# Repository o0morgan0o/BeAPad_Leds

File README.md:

# BeAPad Led Project

Project for touch sensors combined to Neopixels and RTP Midi for controlling Light and music via midiMessages across wifi.

## Materials:

- ESP32 Microcontroller (WROOM
  DEVKIT_V1) [amazon](https://www.amazon.fr/SP-Cow-ESP-32S-d%C3%A9veloppement-Bluetooth-d%C3%A9nergie/dp/B07VJ34N2Q/ref=sr_1_5?__mk_fr_FR=%C3%85M%C3%85%C5%BD%C3%95%C3%91&crid=2QX1H1678O7M3&keywords=esp32+wroom+devkit&qid=1652459031&sprefix=esp32+wroom+devkit%2Caps%2C51&sr=8-5) [aliexpress](https://fr.aliexpress.com/item/1005001929935550.html?spm=a2g0o.search0304.0.0.a4b41103QWyj6D&algo_pvid=caa6f633-4206-442e-8846-f58ec6503b21&algo_exp_id=caa6f633-4206-442e-8846-f58ec6503b21-0&pdp_ext_f=%7B%22sku_id%22%3A%2212000022802021515%22%7D&pdp_npi=2%40dis%21EUR%21%2127.77%21%21%21%21%21%402100bdca16524589488372088ea014%2112000022802021515%21sea)
- MPR121 Touch Shield [amazon](https://www.amazon.fr/Adafruit-12-Key-Capacitive-Sensor-Breakout/dp/B00SK8PVNA)
- WS2812E leds [amazon](https://www.amazon.fr/gp/product/B088BRY2SH/ref=ppx_yo_dt_b_asin_title_o07_s00?ie=UTF8&th=1) **<u>MUST BE 60Leds/m for easy soldering on PCB</u>**
- Battery 1100 mAh Lithium 1S 3c
- 1 Capacitor 1000uF
- Steel plates
- Optional : Power Supply 5V 10A or 4 AA Batteries

## Usage

Use RTP-Midi software in windows to listen for midi signals over Wi-Fi.
(software : https://www.tobias-erichsen.de/software/rtpmidi/rtpmidi-tutorial.html)

Set RTP-Midi device to address `192.168.0.4` (address set to client by ESP32 DHCP)

## Ableton Setup

In order to send midi towards the controller, on each midi track, set an instrument rack with:
- External instrument to RTP_Midi Receiver session
- Your drum rack with active notes mentioned in next section

### Mapping MidiReceive

```
Each MidiNote Receveid is connected to a specific light effect on board
 _______________________________________
|  | | | |  |  | | | | | |  |  | | | |  |
|  | | | |  |  | | | | | |  |  | | | |  |
|  | | | |  |  | | | | | |  |  | | | |  |
|  |_| |_|  |  |_| |_| |_|  |  |_| |_|  |
|   |   |   |   |   |   |   |   |   |   |
|   |   |   |   |   |   |   |   |   |   |
|___|___|___|___|___|___|___|___|___|___|

TOUCH SENSOR BOARDS ARE CONNECTED TO THE FOLLOWING MIDI NOTES:
  The boards always send the same midiNote:
    -> C4 ( MIDI 60 )      Board 1
    -> C#4 ( MIDI 61 )     Board 2
    -> D4 ( MIDI 62 )      Board 3
    -> D#4 ( MIDI 63 )     Board 4
    -> E4 ( MIDI 64 )      Board 5
    -> F4 ( MIDI 65 )      Board 6
    -> F#4 ( MIDI 66 )     Board 7
    -> G4 ( MIDI 67 )      Board 8
    -> G#4 ( MIDI 68 )     Board 9
    -> A4 ( MIDI 69 )      Board 10
    -> A#4 ( MIDI 70 )     Board 11
    
WHEN SHIFT IS PRESSED (BOARD 12) THE SENSOR BOARDS CAN SEND THESE MIDI NOTES:
    ->  G#6 ( MIDI 80 )     Board 1
    ->  A6 ( MIDI 81 )      Board 2
    ->  A#6 ( MIDI 82 )     Board 3
    ->  B6 ( MIDI 83 )      Board 4
    ->  C7 ( MIDI 84 )      Board 5
    ->  C#7 ( MIDI 85 )     Board 6
    ->  D7 ( MIDI 86 )      Board 7
    ->  D#7 ( MIDI 87 )     Board 8
    ->  E7 ( MIDI 88 )      Board 9
    ->  F7 ( MIDI 89 )      Board 10
    ->  F#7 ( MIDI 90 )     Board 11

*****************************
LIGHT_STRATEGIES PER CHANNEL:
-> One color per channel
*****************************
    CHANNEL 1 | FULL_LIGHT
    CHANNEL 2 | FADE_OUT
    CHANNEL 3 | SERPENTIN
    CHANNEL 4 | FLASH_TOWARDS_EXTERIOR
    CHANNEL 5 | NOTHING YET
    CHANNEL 6 | NOTHING YET
    CHANNEL 7 | NOTHING YET
    CHANNEL 8 | NOTHING YET
    
******************************
SPECIAL EFFECTS
-> Color can be change by midi_note value
-> Luminosity can be change by velocity value
******************************

    CHANNEL 9  | STROMBOSCOPE
    CHANNEL 10 | NOTHING YET
    CHANNEL 11 | NOTHING YET
    CHANNEL 12 | NOTHING YET
    CHANNEL 13 | NOTHING YET
    CHANNEL 14 | NOTHING YET
    CHANNEL 15 | NOTHING YET
    CHANNEL 16 | NOTHING YET

```

## Hardware

### LedBoards:

(See EasyEDA project in "Resources_PCB_Schematics")

**Warning: Orientation of led change across the board (see real reference below)**

### Controller Board

(See KiCad project in "Resources_PCB_Schematics")

**Real prototype**

### 3D Models

Very basic holders can be found in Resources_3D_printing.

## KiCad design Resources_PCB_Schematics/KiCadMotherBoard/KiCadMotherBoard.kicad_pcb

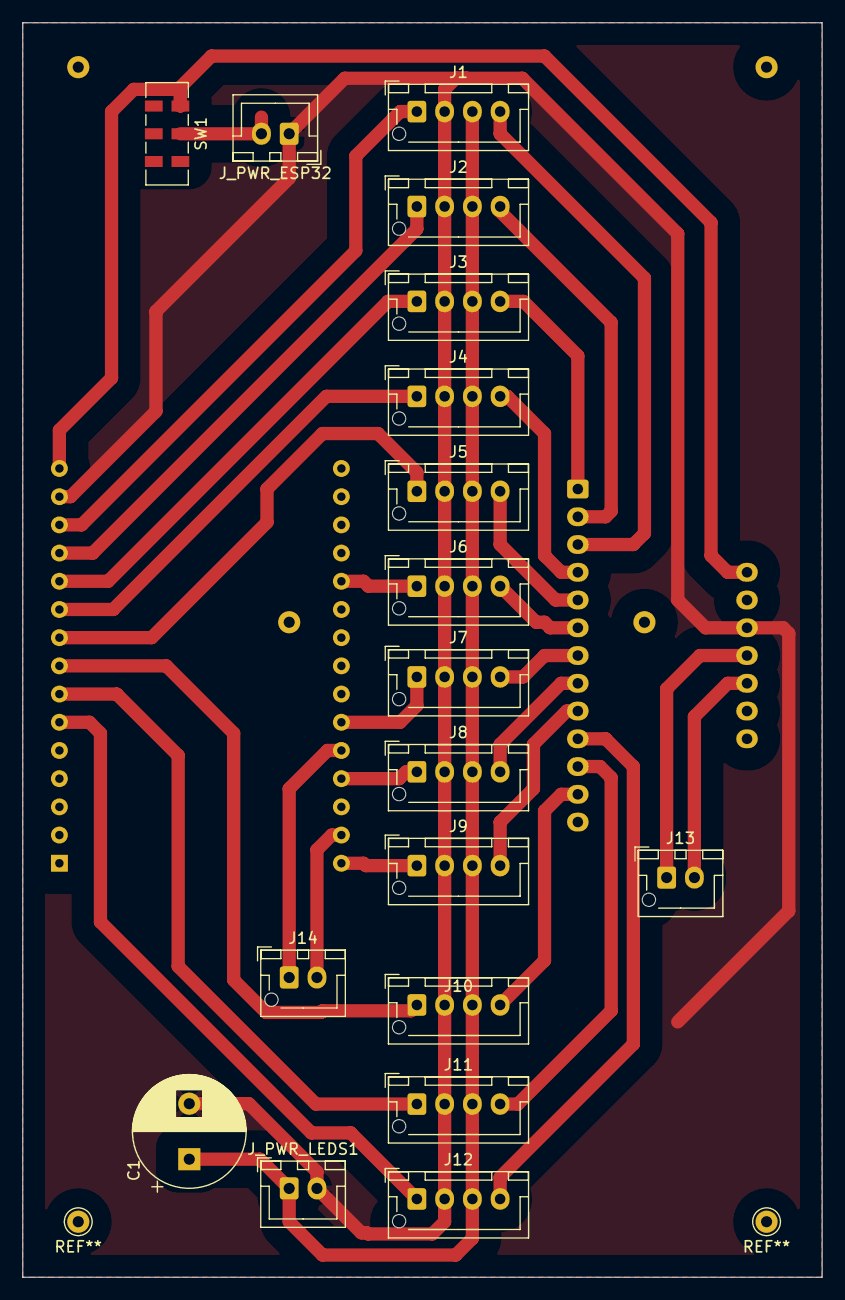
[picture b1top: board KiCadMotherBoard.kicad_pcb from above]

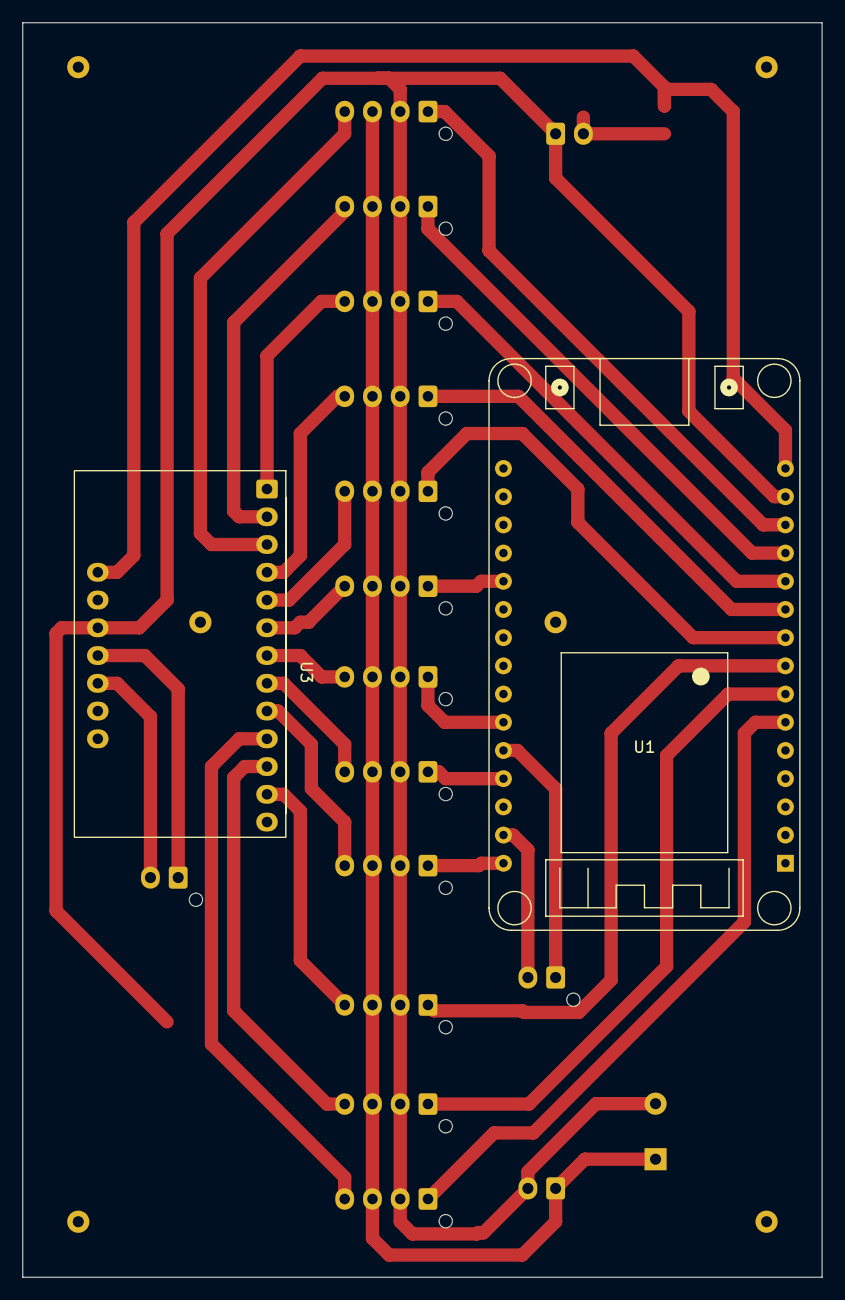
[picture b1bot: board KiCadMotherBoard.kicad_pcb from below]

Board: 2 copper layers, 72.0 x 113.0 mm, 20 parts (2 on the bottom side), 30 nets.

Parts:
C1: 1000uF; CP_Radial_D10.0mm_P5.00mm
J1, J2, J3, J4, J5, J6, J7, J8, J9, J10, J11, J12: Conn_01x04_Male; JST_XH_B4B-XH-AM_1x04_P2.50mm_Vertical
J13, J14: SDA_SCL_BRIDGE; JST_XH_B2B-XH-AM_1x02_P2.50mm_Vertical
J_PWR_ESP32: Conn_01x02_Male; JST_XH_B2B-XH-A_1x02_P2.50mm_Vertical
J_PWR_LEDS1: Conn_01x02_Male; JST_XH_B2B-XH-A_1x02_P2.50mm_Vertical
SW1: SW_SPDT; SW_DPDT_CK_JS202011JCQN
U1: ESP32_DevKit_V1_DOIT_MAIN_CONTROLLER; esp32_devkit_v1_doit
U3: MPR121QR2; custom-mpr121

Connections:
+5V: C1.1, J1.3, J2.3, J3.3, J4.3, J5.3, J6.3, J7.3, J8.3, J9.3, J10.3, J11.3, J12.3, J_PWR_LEDS1.1
/LED_P3: J8.1, U1.27 (RXD0/IO3)
/LED_P4: J6.1, U1.20 (IO4)
/LED_P12: J2.1, U1.12 (IO12)
/LED_P13: J1.1, U1.13 (IO13)
/LED_P14: J3.1, U1.11 (IO14)
/LED_P19: J7.1, U1.25 (IO19)
/LED_P23: J9.1, U1.30 (IO23)
/LED_P25: J10.1, U1.8 (IO25)
/LED_P26: J5.1, U1.9 (IO26)
/LED_P27: J4.1, U1.10 (IO27)
/LED_P32: J12.1, U1.6 (IO32)
/LED_P33: J11.1, U1.7 (IO33)
/SCL: J13.2, J14.2, U1.29 (IO22), U3.2 (SCL)
/SDA: J13.1, J14.1, U1.26 (IO21), U3.3 (SDA)
/TOUCH1: J3.4, U3.8 (ELE0)
/TOUCH2: J2.4, U3.9 (ELE1)
/TOUCH3: J1.4, U3.10 (ELE2)
/TOUCH4: J4.4, U3.11 (ELE3)
/TOUCH5: J5.4, U3.12 (LED0/ELE4)
/TOUCH6: J6.4, U3.13 (LED1/ELE5)
/TOUCH7: J7.4, U3.14 (LED2/ELE6)
/TOUCH8: J8.4, U3.15 (LED3/ELE7)
/TOUCH9: J9.4, U3.16 (LED4/ELE8)
/TOUCH10: J12.4, U3.17 (LED5/ELE9)
/TOUCH11: J11.4, U3.18 (LED6/ELE10)
/TOUCH12: J10.4, U3.19 (LED7/ELE11)
GND: C1.2, J1.2, J2.2, J3.2, J4.2, J5.2, J6.2, J7.2, J8.2, J9.2, J10.2, J11.2, J12.2, J_PWR_ESP32.1, J_PWR_LEDS1.2, U1.14 (GND), U3.6 (VSS)
unnamed: J_PWR_ESP32.2, SW1.2 (B)
VCC: SW1.1 (A), U1.15 (VIN), U3.20 (VDD)

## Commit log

2022-04-22 initialCommit
2022-04-23 functional prototype
2022-04-25 [features] Working on strategies
2022-04-26 [features] Add FadeOut LightStrategy and better handling from manager and main
2022-04-26 [fix] switch to Sync WebServer
2022-04-27 [feature] add rtp_midi and working on fade options for colors
2022-04-30 [intermediary] intermediary commit
2022-05-01 [intermediary] example functional on one led
2022-05-01 [intermediary] example functioel
2022-05-01 [test] minor change
2022-05-01 [test] another minor change
2022-05-01 [test] again change
2022-05-02 done
2022-05-05 update pcb sketches
2022-05-08 Moved to adafruit Neopixel Library, more tests to do. Fast led don't work
2022-05-08 implementing
2022-05-09 [feature] Preparing docs and added TODO for multiple trigger boards on same Midi Note
2022-05-12 add light all boards on shift
2022-05-13 implemented
2022-05-13 done strategyMixer
2022-05-13 minor changes before implementation
2022-05-13 [feature] implementation in progress
2022-05-13 update links in README
2022-05-14 access point not working
2022-05-14 [feature] moved to strategy defined by midiChannel
2022-05-14 minor change
2022-05-15 add tromboscope special effect
2022-05-15 fix tests with previous changes
2022-05-15 [feature] add serpentin LightStrategy
2022-05-15 [feature] add flashTowardsEnd Strategy
2022-05-15 correction in behavior of serpentin at triggerOff
2022-05-16 implement color setting per channel for strategies
2022-05-16 removed unused files
2022-05-17 updated doc + bug fix in main.cpp
2022-05-17 add feature set-threshold for touch and add documentation
2022-05-21 add ableton live example set
2022-05-21 minor changes in comments of main.cpp
2022-05-27 add instructions for color
